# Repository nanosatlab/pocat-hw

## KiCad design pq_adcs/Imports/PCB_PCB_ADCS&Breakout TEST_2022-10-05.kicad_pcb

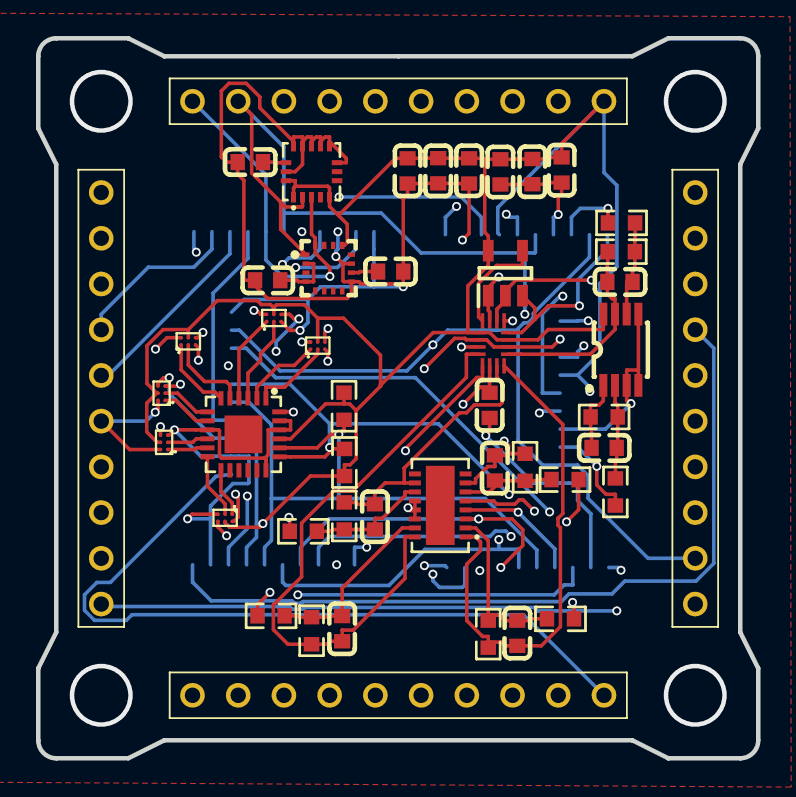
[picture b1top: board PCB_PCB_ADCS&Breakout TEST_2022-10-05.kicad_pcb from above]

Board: 4 copper layers, 40.0 x 40.0 mm, 53 parts (0 on the bottom side), 58 nets.

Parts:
BOT: BOT; 2023961007
C1: 10nF; C0603
C2, C4: 0.47uF; C0603
C3: 0.1uF; C0603
C5, C14, C15: 1uF; C0603
C6: 10u; C0603
C7: 0.1u; C0603
C8, C9, C10, C11, C12, C13: 0.1n; C0603
C16: 1u; C0603
IC2: TMUX1108RSVR; QFN40P180X260X55-16N
IC3: SN74AUP1G08DBVT; SOT95P280X145-5N
J1, J8: LAT; 2023961007
J3: TOP; 2023961107
J11, J12, J13, J14: SLW-110-01-X-S
LAT: LAT; 2023961007
LAT_: LAT; 2023961007
LV1CT, LV3CT, LV4CT, LV5CT, LV6CT, LV7CT: LV8498CT_footprint; WLP-6_L1.30-W0.90-P0.40-TL
R1, R8, R9, R11, R14, R15: 100R; R0603
R2, R6, R7, R10, R12, R13: 2k; R0603
R3: ICG-20330; LGA-16_L3.0-W3.0-P0.50-BL
R4, R5: 2.7K; R0603
U1: MMC5983MA; LGA-16_L3.0-W3.0-P0.50-BL_SQ
U2: LT6005CDHC#TRPBF; DFN-16_L5.0-W3.0-P0.50-BL-EP
U3: PCA9547BS,118; HVQFN-24_L4.0-W4.0-P0.50-BL-EP2.1
U5: LT6004IMS8#PBF; MOSP-8_L3.0-W3.0-P0.65-LS4.9-BL

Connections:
BURNCOMMS: J1.9, J8.9, J13.9, LAT.9, LAT_.9
GND: BOT.2, BOT.4, BOT.9, C1.1, C2.1, C3.1, C4.1, C5.1, C6.2, C7.2, C14.2, C15.2, C16.2, IC2.2, IC2.5, IC2.10, IC2.12, IC3.3, J1.2, J1.7, J1.10, J3.7, J3.9, J3.11, J8.2, J8.7, J8.10, J11.9, LAT.2, LAT.7, LAT.10, LAT_.2, LAT_.7, LAT_.10, LV1CT.C1, LV3CT.C1, LV4CT.C1, LV5CT.C1, LV6CT.C1, LV7CT.C1, R3.8, R3.9, R3.10, R3.11, R3.12, R3.13, R3.15, U1.9, U1.11, U2.3, U2.5, U2.12, U2.13, U2.14, U3.9, U3.18, U3.22, U3.23, U5.3, U5.4, U5.5
IC3_4: IC2.16, IC3.4
IOUT1: J3.10, LV1CT.C2
IOUT2: BOT.8, LV7CT.C2
IOUT3: LAT.3, LV3CT.C2
IOUT4: LAT_.3, LV4CT.C2
IOUT5: J8.3, LV5CT.C2
IOUT6: J1.3, LV6CT.C2
KILLSWITCH: BOT.1, J11.4
NRST: J12.6, LV1CT.A2, LV3CT.A2, LV4CT.A2, LV5CT.A2, LV6CT.A2, LV7CT.A2
PH1_ADCS: C8.2, IC2.8, R2.1, U2.1
PH2_ADCS: C9.2, IC2.3, R6.1, U2.7
PH3_ADCS: C10.1, IC2.4, R7.2, U2.16
PH4_ADCS: C11.1, IC2.7, R10.2, U2.10
PH5_ADCS: C13.2, R13.1, U5.1
PH6_ADCS: C12.2, IC2.9, R12.1, U5.7
PHT1: LAT_.8, R1.1
PHT2: BOT.3, R9.1
PHT3: J3.8, R8.2
PHT4: LAT.8, R11.2
PHT5: J8.8, R15.2
PHT6: J1.8, R14.2
PH_OBC: C14.1, IC2.6, J14.6
R3_14: C2.2, R3.14
R12_2: C12.1, R12.2, R14.1, U5.6
R13_2: C13.1, R13.2, R15.1, U5.2
RST_DRIVERS: J14.7, U3.24
SCL: BOT.5, J1.6, J3.6, J8.6, J11.2, LAT.6, LAT_.6, R3.2, R4.1, U1.1, U3.19
SCL1: LV1CT.A1, U3.2
SCL2: LV7CT.A1, U3.4
SCL3: LV3CT.A1, U3.6
SCL4: LV4CT.A1, U3.8
SCL5: LV5CT.A1, U3.11
SCL6: LV6CT.A1, U3.13
SDA: BOT.6, J1.5, J3.5, J8.5, J11.1, LAT.5, LAT_.5, R3.3, R5.2, U1.16, U3.20
SDA1: LV1CT.B1, U3.1
SDA2: LV7CT.B1, U3.3
SDA3: LV3CT.B1, U3.5
SDA4: LV4CT.B1, U3.7
SDA5: LV5CT.B1, U3.10
SDA6: LV6CT.B1, U3.12
SEL_PH0: IC2.15, IC3.1, J13.5
SEL_PH1: IC2.14, IC3.2, J13.6
SEL_PH2: IC2.13, J14.5
SOLAR_X: J1.1, J12.10, LAT.1
SOLAR_Y: BOT.10, J13.4
SOLAR_Z: J8.1, J14.10, LAT_.1
SWCLK: J3.2, J12.4
SWDIO: J3.3, J12.5
U1_2: C16.1, U1.2, U1.4
U1_10: C6.1, U1.10
U2_2: C8.1, R1.2, R2.2, U2.2
U2_6: C9.1, R6.2, R9.2, U2.6
U2_11: C11.2, R10.1, R11.1, U2.11
U2_15: C10.2, R7.1, R8.1, U2.15
VCC_STM: J3.1, J14.3
VDDIO: BOT.7, C1.2, C3.2, C4.2, C5.2, C7.1, C15.1, IC2.1, IC2.11, IC3.5, J1.4, J3.4, J8.4, J11.10, LAT.4, LAT_.4, LV1CT.B2, LV3CT.B2, LV4CT.B2, LV5CT.B2, LV6CT.B2, LV7CT.B2, R3.1, R3.5, R3.16, R4.2, R5.1, U1.13, U2.4, U3.21, U5.8

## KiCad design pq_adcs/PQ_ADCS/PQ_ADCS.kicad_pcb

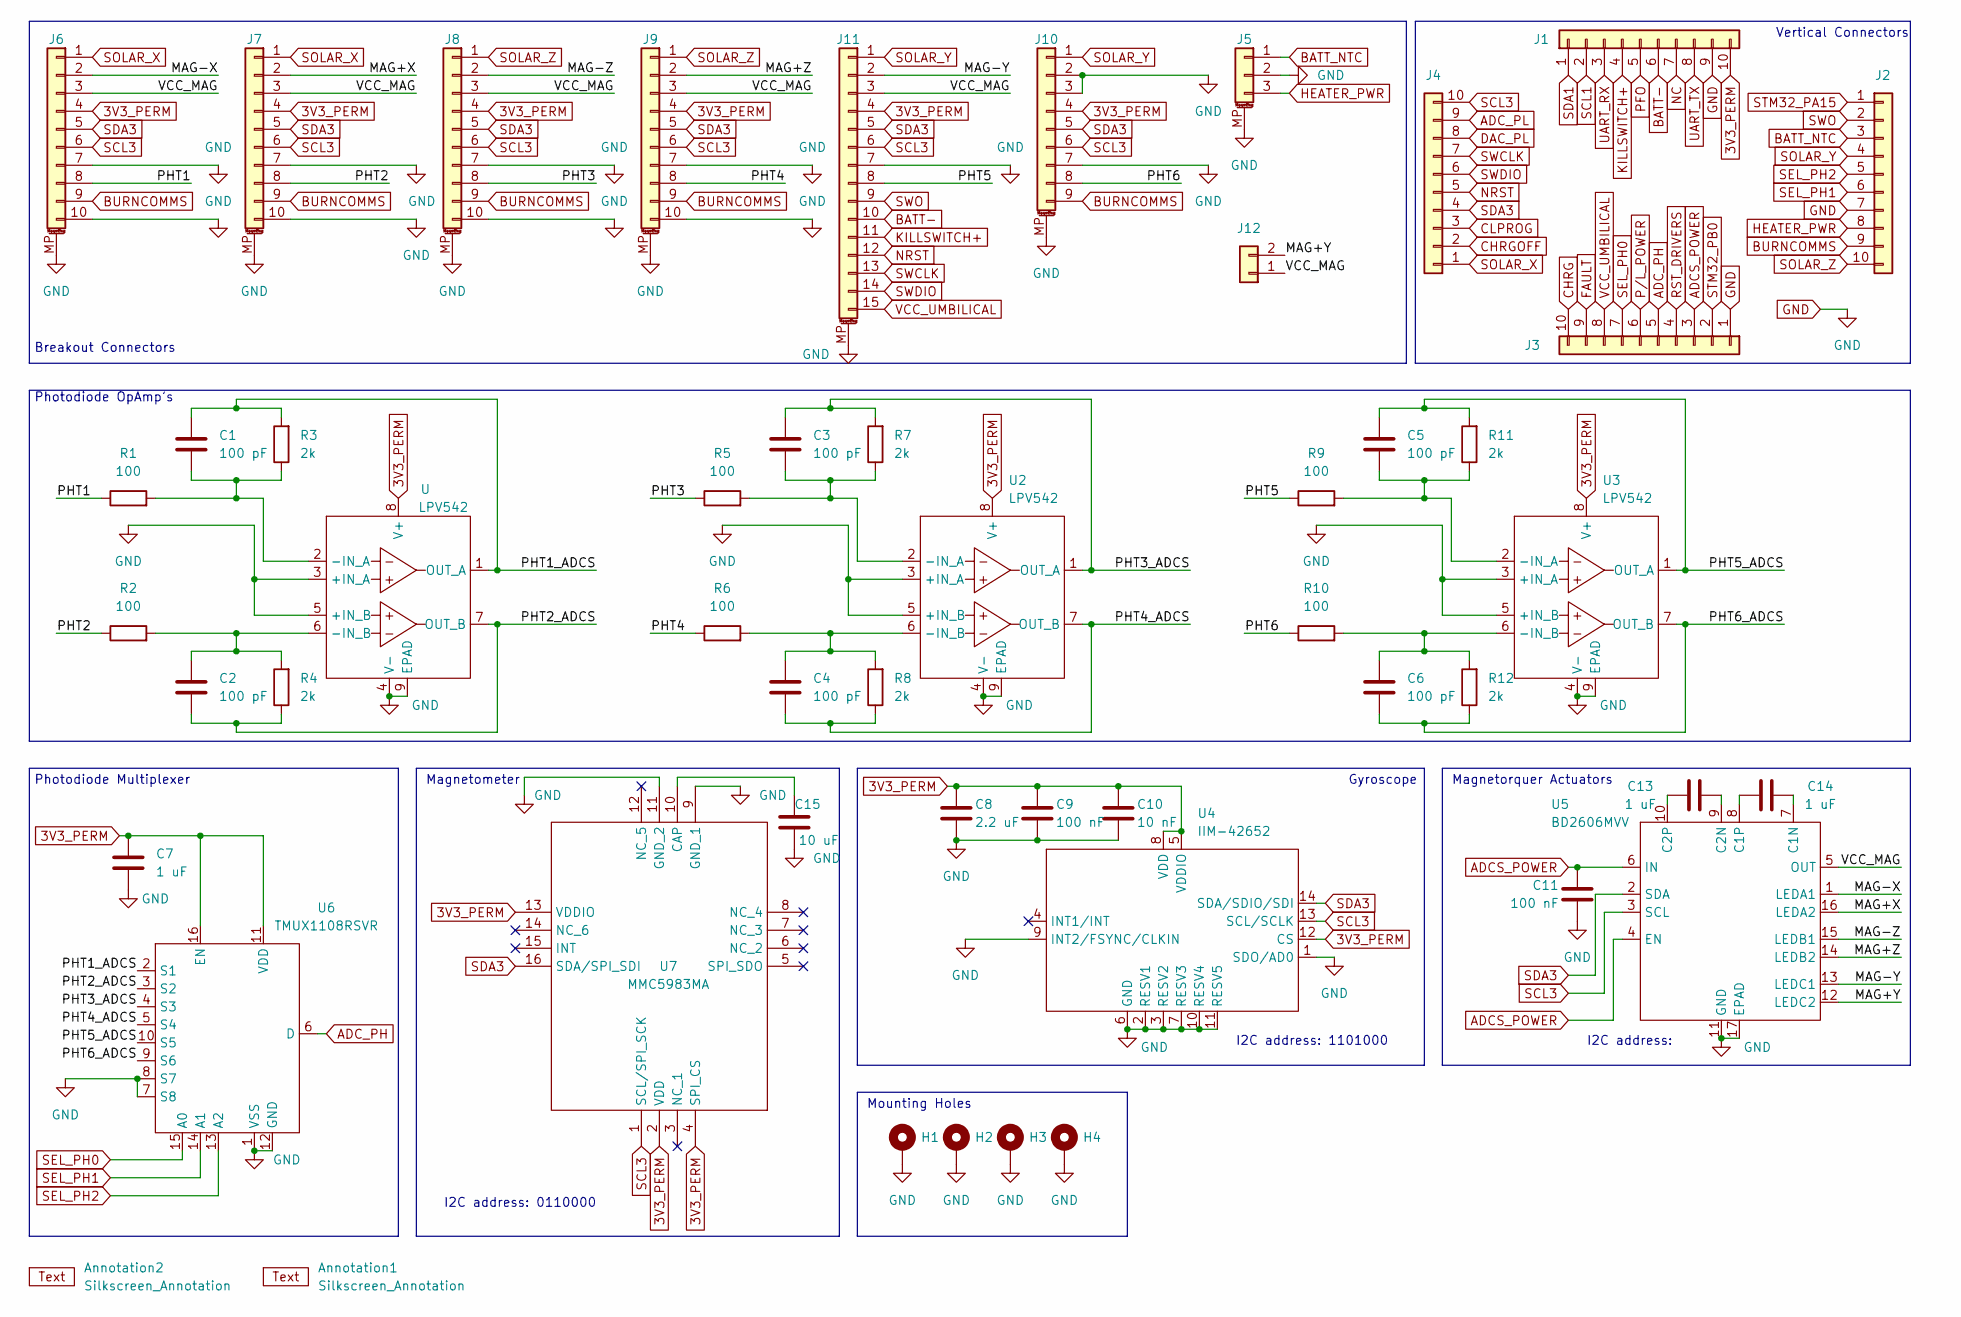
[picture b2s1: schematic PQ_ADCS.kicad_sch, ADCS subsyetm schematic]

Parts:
Annotation1: Silkscreen_Annotation; Bike
Annotation2: Silkscreen_Annotation; Bridgemaker
C1, C2, C3, C4, C5, C6: 100 pF; C_0603_1608Metric; Manufacturer Part Numbe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 06035C101K4T2A
C7, C13, C14: 1 uF; C_0603_1608Metric; Manufacturer Part Numbe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 GRM188R61A105KA61D
C8: 2.2 uF; C_0603_1608Metric; Manufacturer Part Numbe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 GRM033R60J225ME15D
C9, C11: 100 nF; C_0603_1608Metric; Manufacturer Part Numbe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 GRM188R72A104KA35J
C10: 10 nF; C_0603_1608Metric; Manufacturer Part Numbe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 0201YD103KAT4A
C15: 10 uF; C_0805_2012Metric; Manufacturer Part Numbe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 GRM188R72A104KA35J
H1, H2, H3, H4: MountingHole_Pad; MountingHole_3.2mm_M3_Pad; Manufacturer Part Numbe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 N/A
J1, J2, J3, J4: CES-110-02-L-S; SLW-110-01; Manufacturer Part Numbe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 CES-110-02-L-S
J5: Pico-Clasp_01x03; Picoclasp03; Manufacturer Part Numbe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 203556-0307
J6, J7, J8, J9: Pico-Clasp_01x10; Picoclasp10; Manufacturer Part Numbe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 504449-1007
J10: Pico-Clasp_01x09; Picoclasp09; Manufacturer Part Numbe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 504449-0907
J11: Pico-Clasp_01x15; Picoclasp15; Manufacturer Part Numbe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 504449-1507
J12: CES-102-02-L-S; CES-102-02; Manufacturer Part Numbe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 CES-102-02-L-S
R1, R2, R5, R6, R9, R10: 100; R_0603_1608Metric; Manufacturer Part Numbe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 AC0603FR-13100RL
R3, R4, R7, R8, R11, R12: 2k; R_0603_1608Metric; Manufacturer Part Numbe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 RC0603FR-132KL
U, U2, U3: LPV542; TI_X1SON-8_3x3mm; Manufacturer Part Numbe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 LPV542DNXR
U4: IIM-42652; IIM42652; Manufacturer_Part_Number IIM-42652; Mouser Part Number 410-IIM-42652
U5: BD2606MVV; QFN-16-1EP_4x4mm_P0.65mm_EP2.5x2.5mm; Manufacturer Part Numbe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 BD2606MVV-E2
U6: TMUX1108RSVR; UQFN-16_1.8x2.6_Pitch0.4mm; Manufacturer Part Numbe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 TMUX1108RSVR
U7: MMC5983MA; Manufacturer_Part_Number MMC5983MA; Mouser Part Number 438-MMC5983MA

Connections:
3V3_PERM: C7.1, C8.1, C9.1, C10.1, J1.10, J6.4, J7.4, J8.4, J9.4, J10.4, J11.4, U.8 (V+), U2.8 (V+), U3.8 (V+), U4.5 (VDDIO), U4.8 (VDD), U4.12 (CS), U6.11 (VDD), U6.16 (EN), U7.2 (VDD), U7.4 (SPI_CS), U7.13 (VDDIO)
/MAG+X: J7.2, U5.16 (LEDA2)
/MAG+Y: J12.2, U5.12 (LEDC2)
/MAG+Z: J9.2, U5.14 (LEDB2)
/MAG-X: J6.2, U5.1 (LEDA1)
/MAG-Y: J11.2, U5.13 (LEDC1)
/MAG-Z: J8.2, U5.15 (LEDB1)
/PHT1: J6.8, R1.1
/PHT1_ADCS: C1.1, R3.2, U.1 (OUT_A), U6.2 (S1)
/PHT2: J7.8, R2.1
/PHT2_ADCS: C2.2, R4.1, U.7 (OUT_B), U6.3 (S2)
/PHT3: J8.8, R5.1
/PHT3_ADCS: C3.1, R7.2, U2.1 (OUT_A), U6.4 (S3)
/PHT4: J9.8, R6.1
/PHT4_ADCS: C4.2, R8.1, U2.7 (OUT_B), U6.5 (S4)
/PHT5: J11.8, R9.1
/PHT5_ADCS: C5.1, R11.2, U3.1 (OUT_A), U6.10 (S5)
/PHT6_ADCS: C6.2, R12.1, U3.7 (OUT_B), U6.9 (S6)
/VCC_MAG: J6.3, J7.3, J8.3, J9.3, J11.3, J12.1, U5.5 (OUT)
ADCS_POWER: C11.1, J3.3, U5.4 (EN), U5.6 (IN)
ADC_PH: J3.5, U6.6 (D)
ADC_PL: J4.9
BATT-: J1.6, J11.10
BATT_NTC: J2.3, J5.1
BURNCOMMS: J2.9, J6.9, J7.9, J8.9, J9.9, J10.9
CHRG: J3.10
CHRGOFF: J4.2
CLPROG: J4.3
DAC_PL: J4.8
FAULT: J3.9
GND: C7.2, C8.2, C9.2, C10.2, C11.2, C15.2, H1.1, H2.1, H3.1, H4.1, J1.9, J2.7, J3.1, J5.2, J5.MP, J6.7, J6.10, J6.MP, J7.7, J7.10, J7.MP, J8.7, J8.10, J8.MP, J9.7, J9.10, J9.MP, J10.2, J10.3, J10.7, J10.MP, J11.7, J11.MP, U.3 (+IN_A), U.4 (V-), U.5 (+IN_B), U.9 (EPAD), U2.3 (+IN_A), U2.4 (V-), U2.5 (+IN_B), U2.9 (EPAD), U3.3 (+IN_A), U3.4 (V-), U3.5 (+IN_B), U3.9 (EPAD), U4.1 (SDO/AD0), U4.2 (RESV1), U4.3 (RESV2), U4.6 (GND), U4.7 (RESV3), U4.9 (INT2/FSYNC/CLKIN), U4.10 (RESV4), U4.11 (RESV5), U5.11 (GND), U5.17 (EPAD), U6.1 (VSS), U6.7 (S8), U6.8 (S7), U6.12 (GND), U7.9 (GND_1), U7.11 (GND_2)
HEATER_PWR: J2.8, J5.3
KILLSWITCH+: J1.4, J11.11
NRST: J4.5, J11.12
unnamed: C1.2, R1.2, R3.1, U.2 (-IN_A)
unnamed: C2.1, R2.2, R4.2, U.6 (-IN_B)
unnamed: C3.2, R5.2, R7.1, U2.2 (-IN_A)
unnamed: C4.1, R6.2, R8.2, U2.6 (-IN_B)
unnamed: C5.2, R9.2, R11.1, U3.2 (-IN_A)
unnamed: C6.1, R10.2, R12.2, U3.6 (-IN_B)
unnamed: C14.2, U5.7 (C1N)
unnamed: C14.1, U5.8 (C1P)
unnamed: C13.2, U5.9 (C2N)
unnamed: C13.1, U5.10 (C2P)
unnamed: C15.1, U7.10 (CAP)
PFO: J1.5
P/L_POWER: J3.6
SCL1: J1.2
SDA1: J1.1
SDA3: J4.4, J6.5, J7.5, J8.5, J9.5, J10.5, J11.5, U4.14 (SDA/SDIO/SDI), U5.2 (SDA), U7.16 (SDA/SPI_SDI)
SEL_PH0: J3.7, U6.15 (A0)
SEL_PH1: J2.6, U6.14 (A1)
SEL_PH2: J2.5, U6.13 (A2)
SOLAR_X: J4.1, J6.1, J7.1
SOLAR_Y: J2.4, J10.1, J11.1
SOLAR_Z: J2.10, J8.1, J9.1
STM32_PA9: J3.4
STM32_PA15: J2.1
STM32_PB0: J3.2
SWCLK: J4.7, J11.13
SWDIO: J4.6, J11.14
SWO: J2.2, J11.9
UART_RX: J1.3
UART_TX: J1.8
VCC_UMBILICAL: J3.8, J11.15

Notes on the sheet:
Mounting Holes
Breakout Connectors
I2C address: 1101000
Photodiode Multiplexer
I2C address:
Gyroscope
I2C address: 0110000
Photodiode OpAmp's
Magnetorquer Actuators
Vertical Connectors
Magnetometer

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
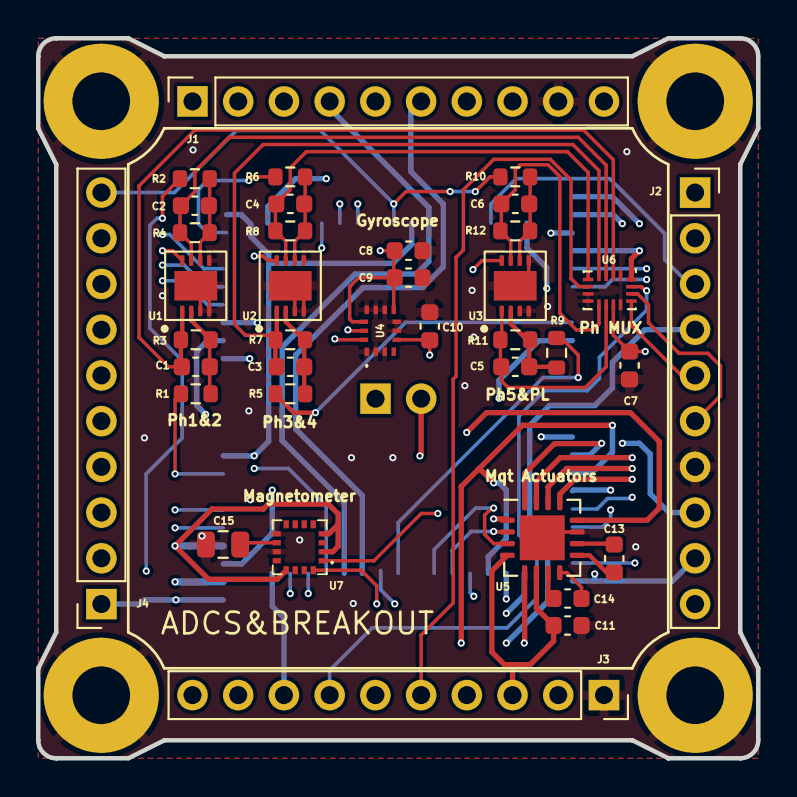
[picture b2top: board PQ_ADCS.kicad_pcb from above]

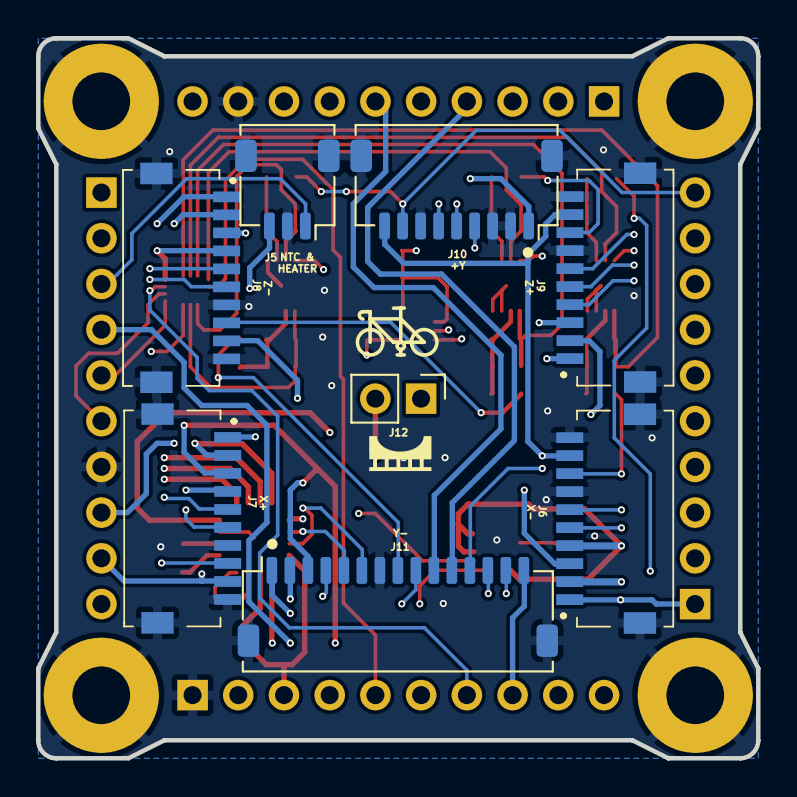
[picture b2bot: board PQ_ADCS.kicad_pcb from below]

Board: 6 copper layers, 40.0 x 40.0 mm, 51 parts (10 on the bottom side), 52 nets.

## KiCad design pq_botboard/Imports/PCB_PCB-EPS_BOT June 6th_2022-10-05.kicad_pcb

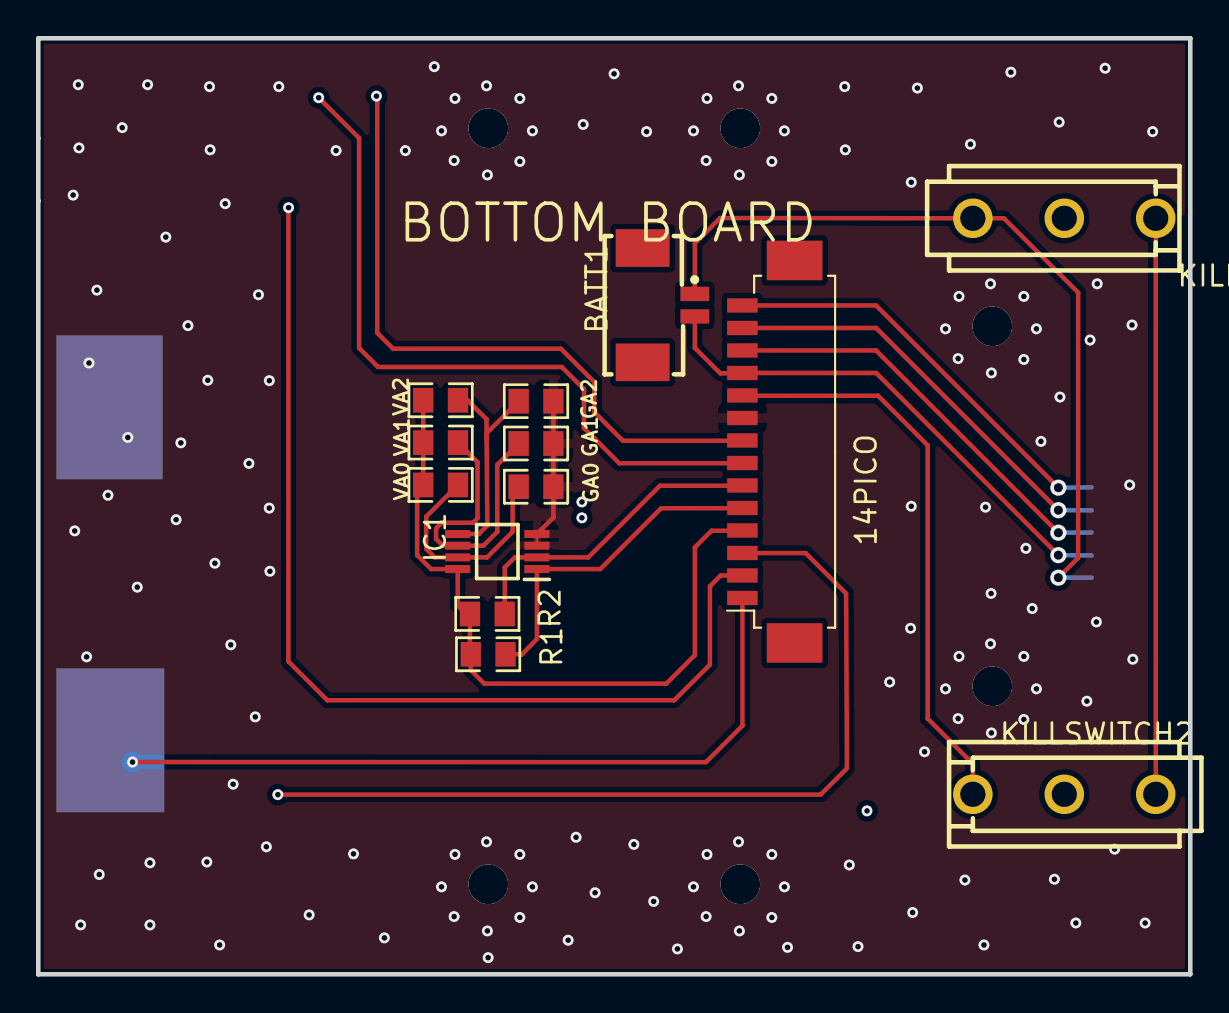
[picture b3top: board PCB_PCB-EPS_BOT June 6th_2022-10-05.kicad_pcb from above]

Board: 6 copper layers, 64.0 x 52.0 mm, 15 parts (0 on the bottom side), 17 nets.

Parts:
14PICO: REF; MOLEX_PICOBLADE_53261-1471_14X1.25MM_ANGLED
BATT1: CONN-SMD_532610271
GA0, GA1, GA2: 5k; R0805
IC1: TCN75AVUA713-VAO; SOP65P490X110-8N
J1: MOLEX 0533980667
KILLSWITCH1, KILLSWITCH2: SW-TH_D2F-01L
PHT: SLCD-61N8
R1, R2: 5k; R0805
VA0, VA1, VA2: 5k; R0805

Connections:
ADCS: 14PICO.2, 14PICO.3
BATT+: BATT1.1, J1.6, KILLSWITCH1.3
BATT-: 14PICO.11, BATT1.2, J1.5
GND: 14PICO.9, GA0.1, GA1.1, GA2.1, IC1.3, IC1.4
IC1_5: GA2.2, IC1.5, VA2.1
IC1_6: GA1.2, IC1.6, VA1.1
IC1_7: GA0.2, IC1.7, VA0.1
KILLSWITCH: 14PICO.10, KILLSWITCH2.1
PHOTODIODE: 14PICO.8, PHT.1
PHOTODIODE_GND: 14PICO.7, PHT.2
S$18611: KILLSWITCH1.1, KILLSWITCH2.3
SCL: 14PICO.6, IC1.2, R2.1
SDA: 14PICO.5, IC1.1, R1.1
SWCLK: 14PICO.13, J1.3
SWDIO: 14PICO.14, J1.2
VCC: 14PICO.4, IC1.8, R1.2, R2.2, VA0.2, VA1.2, VA2.2
VCC_STM: 14PICO.12, J1.4

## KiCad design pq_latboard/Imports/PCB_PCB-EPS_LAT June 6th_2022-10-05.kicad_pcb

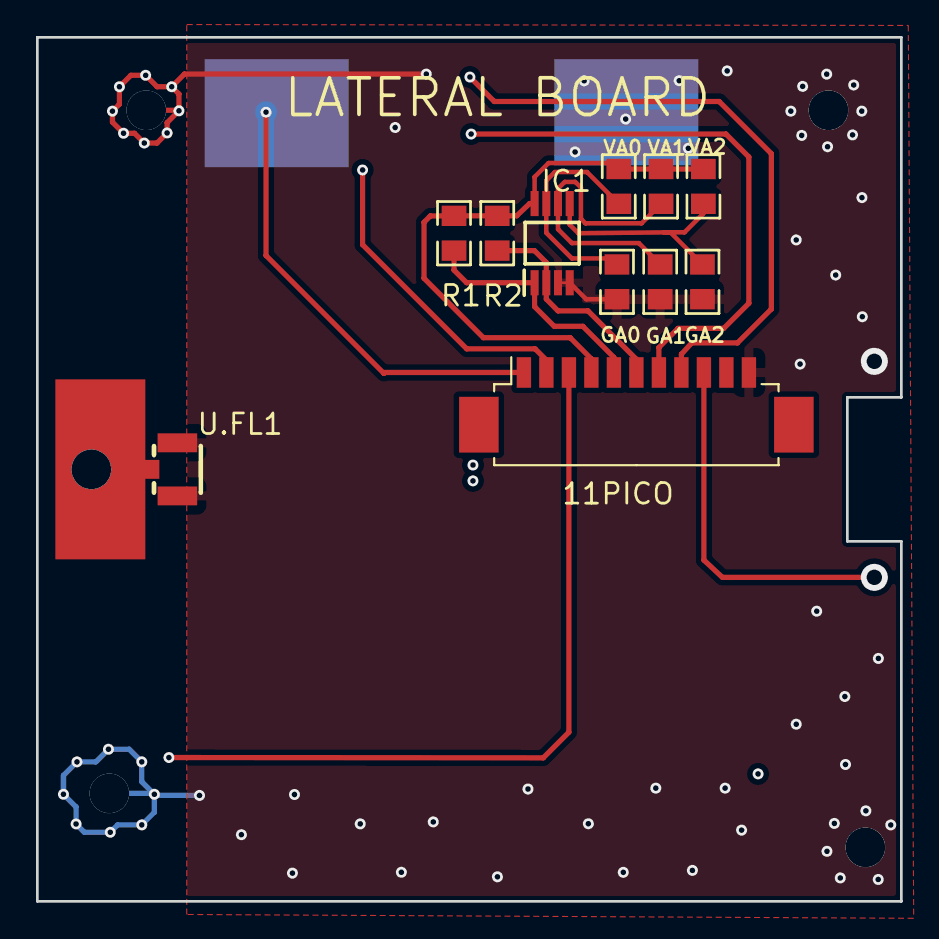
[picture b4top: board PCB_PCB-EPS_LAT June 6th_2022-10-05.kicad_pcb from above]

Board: 6 copper layers, 48.0 x 48.0 mm, 12 parts (0 on the bottom side), 10 nets.

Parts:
11PICO: REF; MOLEX_PICOBLADE_53261-1171_11X1.25MM_ANGLED
GA0, GA1, GA2: 5k; R0805
IC1: TCN75AVUA713-VAO; SOP65P490X110-8N
R1, R2: 5k; R0805
U6: SLCD-61N8
U.FL1: U.FL-R-SMT-1_10_; U.FL-R-SMT-1(10)
VA0, VA1, VA2: 5k; R0805

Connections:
ADCS: 11PICO.2, 11PICO.3
GND: 11PICO.11, GA0.1, GA1.1, GA2.1, IC1.3, IC1.4, U.FL1.1, U.FL1.2
IC1_5: GA2.2, IC1.5, VA2.1
IC1_6: GA1.2, IC1.6, VA1.1
IC1_7: GA0.2, IC1.7, VA0.1
PHOTODIODE: 11PICO.8, U6.1
PHOTODIODE_GND: 11PICO.7, U6.2
SCL: 11PICO.6, IC1.2, R2.1
SDA: 11PICO.5, IC1.1, R1.1
VCC: 11PICO.4, IC1.8, R1.2, R2.2, VA0.2, VA1.2, VA2.2

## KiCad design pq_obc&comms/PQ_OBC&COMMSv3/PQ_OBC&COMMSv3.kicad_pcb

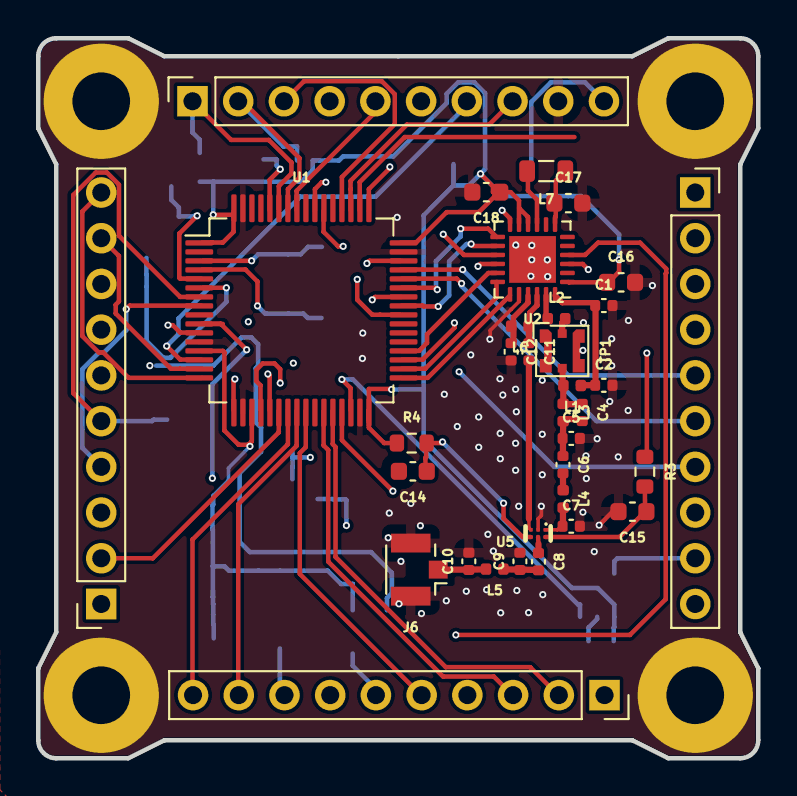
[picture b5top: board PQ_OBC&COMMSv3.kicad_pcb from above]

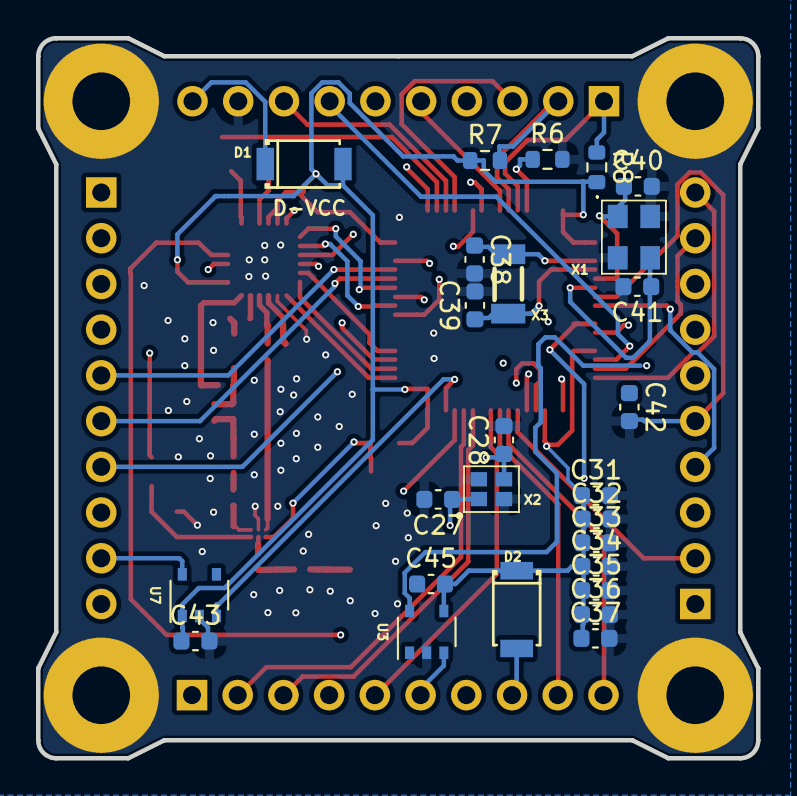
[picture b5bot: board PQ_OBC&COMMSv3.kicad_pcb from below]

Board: 4 copper layers, 40.0 x 40.0 mm, 64 parts (21 on the bottom side), 61 nets.

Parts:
C1: 47nF; C_0402_1005Metric
C2: 47pF; C_0402_1005Metric
C4, C9, C10: 3.3pF; C_0402_1005Metric
C5: 5.6pF; C_0402_1005Metric
C6, C8: 39pF; C_0402_1005Metric
C7: 2.2pF; C_0402_1005Metric
C11: 2.4pF; C_0402_1005Metric
C12: 1.8pF; C_0402_1005Metric
C14, C15: 1nF; C_0603_1608Metric
C16, C37, C43, C45: 1uF; C_0603_1608Metric
C17: 470nF; C_0603_1608Metric
C18, C28, C32, C33, C34, C35, C36, C42: 100nF; C_0603_1608Metric
C27, C38, C39: 10pF; C_0603_1608Metric
C31: 4.7uF; C_0603_1608Metric
C40, C41: 20pF; C_0603_1608Metric
D1: VCC; SOD-128_L3.7-W2.5-LS4.7-FD
D2: VCC_TEST; SOD-128_L3.7-W2.5-LS4.7-FD
H1, H2, H3, H4: MountingHole_Pad; MountingHole_3.2mm_M3_Pad
J1, J2, J3, J4: Conn_01x10; PinSocket_1x10_P2.54mm_Vertical
J6: U.FL-R-SMT-1_10; U.FL_Hirose_U.FL-R-SMT-1_Vertical
L1: 47nH; L_0402_1005Metric
L2: 0R; L_0402_1005Metric
L3: 2.5nH; L_0402_1005Metric
L4: 4.7nH; L_0402_1005Metric
L5: 9.1nH; L_0402_1005Metric
L6: 15nH; L_0402_1005Metric
L7: 15uH; L_0805_2012Metric
R3, R4: 100R; R_0603_1608Metric
R6: 10k; R_0603_1608Metric
R7, R8: 4.7k; R_0603_1608Metric
TP1: CoaxialSwitch_Testpoint; CoaxialSwitch_Hirose_MS-156C3_Horizontal
U1: STM32L476RGTx; LQFP-64_10x10mm_P0.5mm
U2: SX1262IMLTRT; QFN-24-1EP_4x4mm_P0.5mm_EP2.6x2.6mm
U3, U7: BD2232G-GTR; TSOP-5_1.65x3.05mm_P0.95mm
U5: RFswitch; TSNP-6_L1.1-W0.7-P0.40-BR
X1: 12MHz; ECS1201833JEMTR3
X2: FA-128_32.0000MF20X-K5; FA128320000MF20XK5
X3: 32.768KHz; CRYSTAL-SMD_L4.1-W1.5

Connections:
/Boot0: R6.1, U1.60 (BOOT0)
/DIO1: U1.43 (PA10), U2.13 (DIO1)
/MISO: U1.35 (PB14), U2.16 (MISO)
/MOSI: U1.36 (PB15), U2.17 (MOSI)
/PoL_BURN_EN: U1.30 (PB11), U7.3 (EN/EN#)
/PoL_P/L_EN: U1.11 (PC3), U3.3 (EN/EN#)
/RFswitch_ctrl: C15.1, R3.2, U5.6 (CTRL)
/SCK: U1.34 (PB13), U2.18 (SCK)
/SX1262_NRST: U1.40 (PC9), U2.15 (NRESET)
/SX1262_NSS: U1.33 (PB12), U2.19 (NSS)
/XTA: C28.1, U2.3 (XTA), X2.3
/XTB: C27.1, U2.4 (XTB), X2.1
ADC_PH: J4.5, U1.25 (PC5)
ADC_PL: J2.9, U1.15 (PA1)
BURNCOMMS: J3.9, U7.5 (OUT)
CHRG: J4.10, U1.28 (PB2)
CLPROG: J2.3, U1.20 (PA4)
DAC_PL: J2.8, U1.21 (PA5)
FAULT: J4.9, U1.24 (PC4)
GND: C1.2, C2.2, C5.2, C7.2, C9.2, C10.2, C12.2, C14.2, C15.2, C16.2, C17.2, C18.2, C27.2, C28.2, C31.2, C32.2, C33.2, C34.2, C35.2, C36.2, C37.2, C38.2, C39.2, C40.2, C41.2, C42.2, C43.2, C45.1, H1.1, H2.1, H3.1, H4.1, J1.9, J6.2 (Ext), R6.2, TP1.G, U1.12 (VSSA), U1.18 (VSS), U1.31 (VSS), U1.47 (VSS), U1.63 (VSS), U2.2 (GND), U2.5 (GND), U2.8 (GND), U2.20 (GND), U2.25 (GND), U3.2 (GND), U5.2 (GND), U7.2 (GND), X1.2 (GND_1), X1.4 (GND_2), X2.2, X2.4
HEATER_EN: J3.7, U1.29 (PB10)
NRST: C42.1, J2.5, U1.7 (NRST)
unnamed: C1.1, C2.1, L1.1, U2.24 (VR_PA)
unnamed: C4.1, L1.2, L3.1, TP1.A
unnamed: C4.2, C5.1, C6.1, L3.2
unnamed: C6.2, L4.1
unnamed: C7.1, L4.2, U5.1 (RF2)
unnamed: C8.1, U5.5 (RFIN)
unnamed: C8.2, C9.1, L5.1
unnamed: C11.1, L6.1, U2.22 (RFI_N)
unnamed: C11.2, U5.3 (RF1)
unnamed: C12.1, L6.2, U2.21 (RFI_P)
unnamed: C17.1, L7.1, U2.7 (VREG)
unnamed: C10.1, J6.1 (In), L5.2
unnamed: L2.1, U2.23 (RFO)
unnamed: L2.2, TP1.C
unnamed: L7.2, U2.9 (DCC_SW)
unnamed: R3.1, U2.12 (DIO2)
unnamed: C14.1, R4.2
OSC32_IN: C38.1, U1.3 (PC14), X3.1
OSC32_OUT: C39.1, U1.4 (PC15), X3.2
OSC_IN: U1.5 (PH0), X1.1 (IN/OUT)
OSC_OUT: C41.1, U1.6 (PH1), X1.3 (OUT/IN)
PFO: J1.5, U1.57 (PB5)
P/L_POWER: J4.6, U3.5 (OUT)
RST_DRIVERS: J4.4, U1.42 (PA9)
SCL: J1.2, R7.2, U1.58 (PB6)
SDA: J1.1, R8.2, U1.59 (PB7)
SEL_PH1: J3.6, U1.44 (PA11)
SEL_PH2: J3.5, U1.45 (PA12)
STM32_PA2: J2.10, U1.16 (PA2)
STM32_PA15: J3.1, U1.50 (PA15)
STM32_PB3: J3.2, U1.55 (PB3)
STM32_PD2: J3.3, U1.54 (PD2)
SWCLK: J2.7, U1.49 (PA14)
SWDIO: J2.6, U1.46 (PA13)
TOTAL_CURRENT: J1.7, U1.14 (PA0)
UART_RX: J1.3, U1.52 (PC11)
UART_TX: J1.8, U1.51 (PC10)
VCC: C16.1, C18.1, C31.1, C32.1, C33.1, C34.1, C35.1, C36.1, C37.1, C43.1, C45.2, D1.1 (A), J1.10, R4.1, R7.1, R8.1, U1.1 (VBAT), U1.13 (VDDA), U1.19 (VDD), U1.32 (VDD), U1.48 (VDDUSB), U1.64 (VDD), U2.1 (VDD_IN), U2.10 (VBAT), U2.11 (VBAT_IO), U3.1 (IN), U7.1 (IN)
VCC_UMBILICAL: D1.2 (K), J4.8

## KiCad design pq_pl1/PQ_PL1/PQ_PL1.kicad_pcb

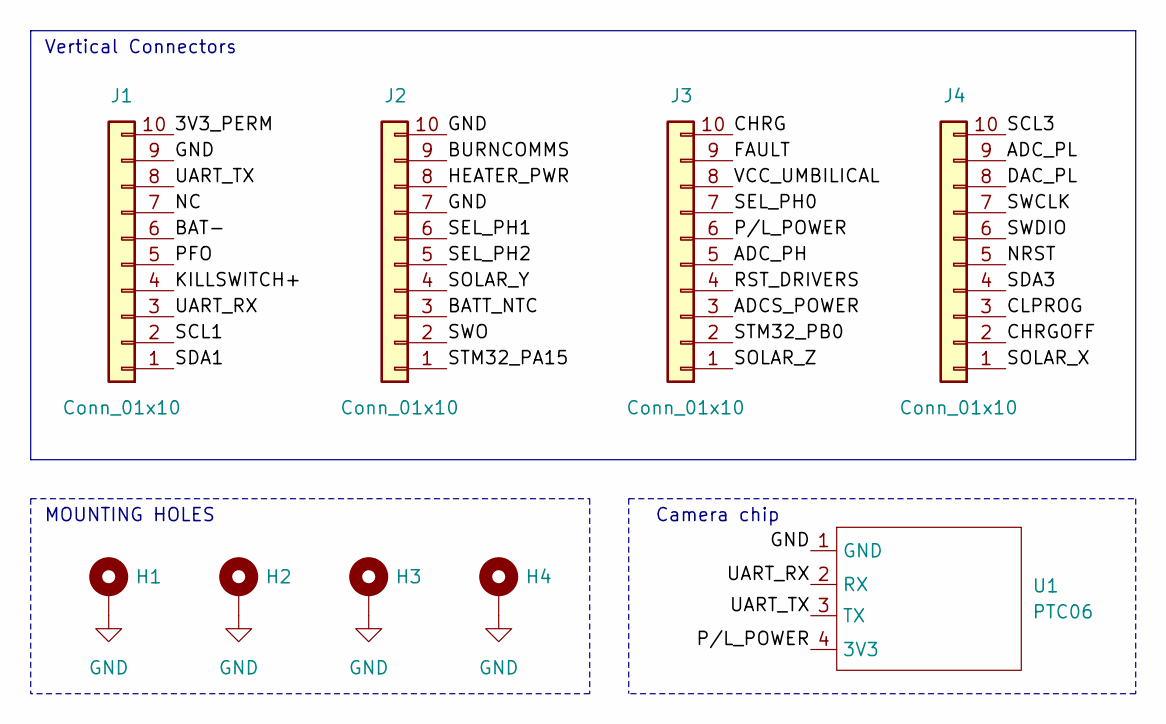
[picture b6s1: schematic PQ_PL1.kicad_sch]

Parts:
H1, H2, H3, H4: MountingHole_Pad; MountingHole_3.2mm_M3_Pad
J1, J2, J3, J4: Conn_01x10; BBL-110-Y-X
U1: PTC06

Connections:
/3V3_PERM: J1.10
/ADCS_POWER: J3.3
/ADC_PH: J3.5
/ADC_PL: J4.9
/BAT-: J1.6
/BATT_NTC: J2.3
/BURNCOMMS: J2.9
/CHRG: J3.10
/CHRGOFF: J4.2
/CLPROG: J4.3
/DAC_PL: J4.8
/FAULT: J3.9
/HEATER_PWR: J2.8
/KILLSWITCH+: J1.4
/NC: J1.7
/NRST: J4.5
/PFO: J1.5
/P/L_POWER: J3.6, U1.4 (3V3)
/RST_DRIVERS: J3.4
/SCL1: J1.2
/SCL3: J4.10
/SDA1: J1.1
/SDA3: J4.4
/SEL_PH0: J3.7
/SEL_PH1: J2.6
/SEL_PH2: J2.5
/SOLAR_X: J4.1
/SOLAR_Y: J2.4
/SOLAR_Z: J3.1
/STM32_PA15: J2.1
/STM32_PB0: J3.2
/SWCLK: J4.7
/SWDIO: J4.6
/SWO: J2.2
/UART_RX: J1.3, U1.2 (RX)
/UART_TX: J1.8, U1.3 (TX)
/VCC_UMBILICAL: J3.8
GND: H1.1, H2.1, H3.1, H4.1, J1.9, J2.7, J2.10, U1.1 (GND)

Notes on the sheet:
MOUNTING HOLES
Camera chip
Vertical Connectors

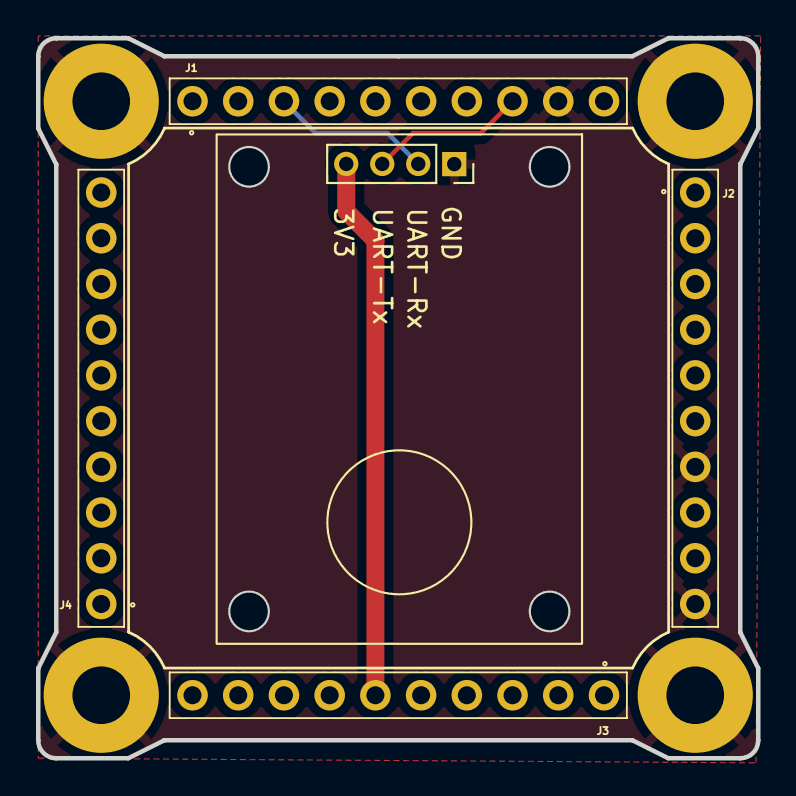
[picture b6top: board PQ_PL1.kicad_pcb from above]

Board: 2 copper layers, 40.0 x 40.0 mm, 9 parts (0 on the bottom side), 4 nets.
